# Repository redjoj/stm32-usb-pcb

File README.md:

# stm32-usb-pcb
This is an STM32-based PCB including USB for power.

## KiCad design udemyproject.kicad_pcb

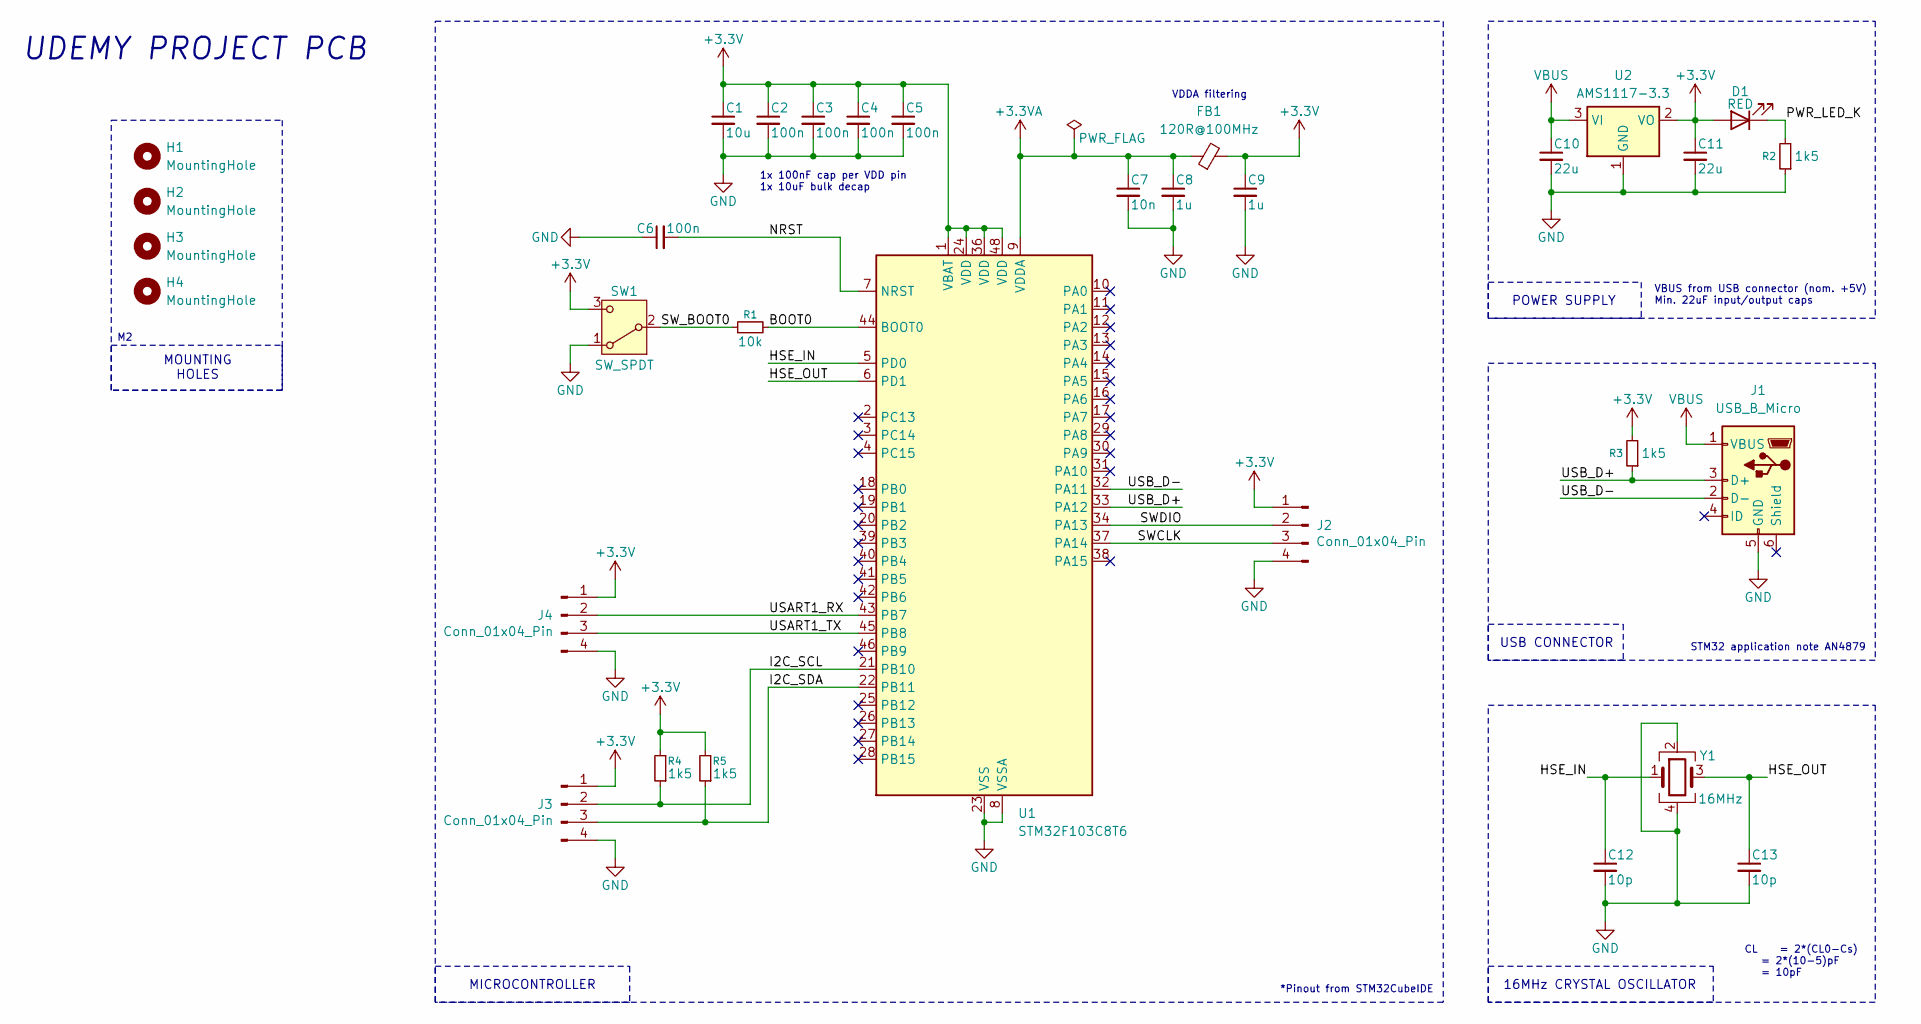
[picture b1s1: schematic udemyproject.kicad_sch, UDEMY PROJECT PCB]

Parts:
C1: 10u; C_0603_1608Metric
C2, C3, C4, C5, C6: 100n; C_0402_1005Metric
C7: 10n; C_0402_1005Metric
C8, C9: 1u; C_0402_1005Metric
C10, C11: 22u; C_0805_2012Metric
C12, C13: 10p; C_0402_1005Metric
D1: RED; LED_0603_1608Metric
FB1: 120R@100MHz; L_0603_1608Metric
H1, H2, H3, H4: MountingHole; MountingHole_2.2mm_M2
J1: USB_B_Micro; USB_Micro-B_Wuerth_629105150521
J2, J3, J4: Conn_01x04_Pin; PinHeader_1x04_P2.54mm_Vertical
R1: 10k; R_0402_1005Metric
R2, R3, R4, R5: 1k5; R_0402_1005Metric
SW1: SW_SPDT; SW_SPDT_PCM12
U1: STM32F103C8T6; LQFP-48_7x7mm_P0.5mm
U2: AMS1117-3.3; SOT-223-3_TabPin2
Y1: 16MHz; Crystal_SMD_3225-4Pin_3.2x2.5mm

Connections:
+3.3V: C1.1, C2.1, C3.1, C4.1, C5.1, C9.1, C11.1, D1.2 (A), FB1.2, J2.1, J3.1, J4.1, R3.2, R4.2, R5.2, SW1.3 (C), U1.1 (VBAT), U1.24 (VDD), U1.36 (VDD), U1.48 (VDD), U2.2 (VO)
+3.3VA: C7.1, C8.1, FB1.1, U1.9 (VDDA)
/BOOT0: R1.2, U1.44 (BOOT0)
/HSE_IN: C12.1, U1.5 (PD0), Y1.1
/HSE_OUT: C13.1, U1.6 (PD1), Y1.3
/I2C_SCL: J3.2, R4.1, U1.21 (PB10)
/I2C_SDA: J3.3, R5.1, U1.22 (PB11)
/NRST: C6.2, U1.7 (NRST)
/PWR_LED_K: D1.1 (K), R2.2
/SWCLK: J2.3, U1.37 (PA14)
/SWDIO: J2.2, U1.34 (PA13)
/SW_BOOT0: R1.1, SW1.2 (B)
/USART1_RX: J4.2, U1.43 (PB7)
/USART1_TX: J4.3, U1.45 (PB8)
/USB_D+: J1.3 (D+), R3.1, U1.33 (PA12)
/USB_D-: J1.2 (D-), U1.32 (PA11)
GND: C1.2, C2.2, C3.2, C4.2, C5.2, C6.1, C7.2, C8.2, C9.2, C10.2, C11.2, C12.2, C13.2, J1.5 (GND), J2.4, J3.4, J4.4, R2.1, SW1.1 (A), U1.8 (VSSA), U1.23 (VSS), U1.35 (VSS), U1.47 (VSS), U2.1 (GND), Y1.2, Y1.4
VBUS: C10.1, J1.1 (VBUS), U2.3 (VI)

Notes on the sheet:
UDEMY PROJECT PCB
VBUS from USB connector (nom. +5V) Min. 22uF input/output caps
1x 100nF cap per VDD pin 1x 10uF bulk decap
USB CONNECTOR
MICROCONTROLLER
VDDA filtering
*Pinout from STM32CubeIDE
CL = 2*(CL0-Cs) = 2*(10-5)pF = 10pF
MOUNTING HOLES
POWER SUPPLY
16MHz CRYSTAL OSCILLATOR
STM32 application note AN4879

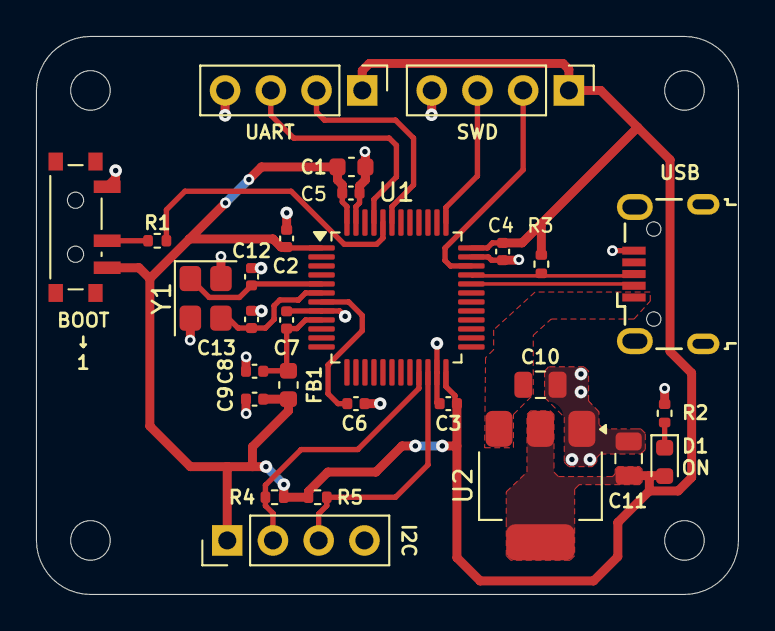
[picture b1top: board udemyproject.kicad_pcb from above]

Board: 2 copper layers, 39.0 x 31.0 mm, 32 parts (0 on the bottom side), 18 nets.

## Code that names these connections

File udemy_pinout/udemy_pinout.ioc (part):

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Mcu.Name=STM32F103C(8-B)Tx
Mcu.Package=LQFP48
Mcu.UserName=STM32F103CBTx
PA0-WKUP.Mode=SYS_WakeUp0
PA0-WKUP.Signal=SYS_WKUP
PA11.Mode=Device
PA11.Signal=USB_DM
PA12.Mode=Device
PA12.Signal=USB_DP
PA13.Mode=Serial_Wire
PA13.Signal=SYS_JTMS-SWDIO
PA14.Mode=Serial_Wire
PA14.Signal=SYS_JTCK-SWCLK
PB10.Mode=I2C
PB10.Signal=I2C2_SCL
PB11.Mode=I2C
PB11.Signal=I2C2_SDA
PB6.Mode=Asynchronous
PB6.Signal=USART1_TX
PB7.Mode=Asynchronous
PB7.Signal=USART1_RX
PD0-OSC_IN.Mode=HSE-External-Oscillator
PD0-OSC_IN.Signal=RCC_OSC_IN
PD1-OSC_OUT.Mode=HSE-External-Oscillator
PD1-OSC_OUT.Signal=RCC_OSC_OUT
board=custom

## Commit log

2026-02-13 Add description for STM32 USB PCB project
2026-02-13 Fix typo in README description
2026-02-13 Added KiCad project to repo.
2026-02-13 Removed STM32CubeIDE files.
